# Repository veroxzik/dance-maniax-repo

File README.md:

# Dance Maniax Repo

A collection of Dance Maniax related items, both from the arcade cabinet and DIY.

**Disclaimer:** I am measuring all these parts by hand, so they may not be 100% accurate (although I try hard). There's no warranty given to anything contained in this repo, so use at your own risk!

## CAD

So far, I only have CAD of the lower sensor assembly. It's uploaded in \*.f3z and \*.stp file.

For planning purposes, I've also included the following image for approximate sensor locations, relative to each other.

## Boards

Likewise, only the boards in the sensor assembly have been reverse engineered.

GX874-PWB(J) is the board which diverts power to the LEDs.

GX874-PWB(I) provides a mounting point for the LEDs and their connector.

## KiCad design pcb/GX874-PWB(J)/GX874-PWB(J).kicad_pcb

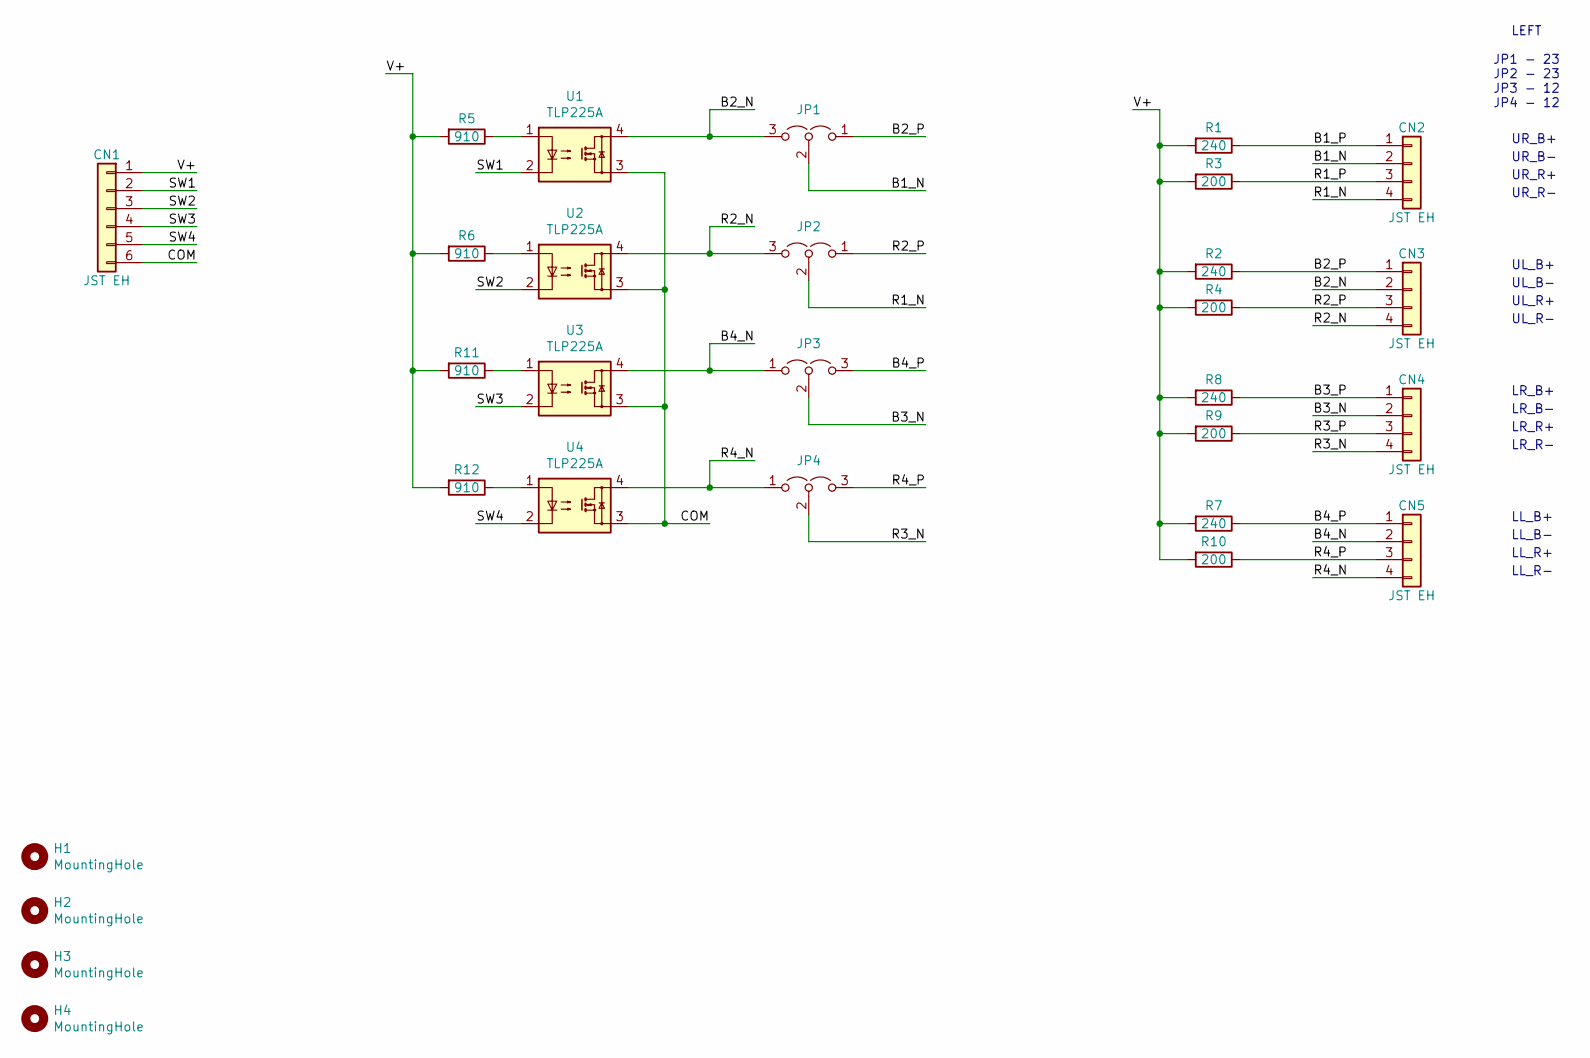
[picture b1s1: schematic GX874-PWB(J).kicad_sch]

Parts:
CN1: JST EH; JST_EH_B6B-EH-A_1x06_P2.50mm_Vertical
CN2, CN3, CN4, CN5: JST EH; JST_EH_B4B-EH-A_1x04_P2.50mm_Vertical
H1, H2, H3, H4: MountingHole; MountingHole_3.2mm_M3_DIN965
JP1, JP2, JP3, JP4: Jumper_3_Open; PinHeader_1x03_P2.54mm_Vertical
R1, R2, R7, R8: 240; R_Axial_DIN0207_L6.3mm_D2.5mm_P10.16mm_Horizontal
R3, R4, R9, R10: 200; R_Axial_DIN0207_L6.3mm_D2.5mm_P10.16mm_Horizontal
R5, R6, R11, R12: 910; R_Axial_DIN0207_L6.3mm_D2.5mm_P10.16mm_Horizontal
U1, U2, U3, U4: TLP225A; DIP-4_W7.62mm

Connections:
/B1_N: CN2.2, JP1.2 (C)
/B1_P: CN2.1, R1.1
/B2_N: CN3.2, JP1.3 (B), U1.4
/B2_P: CN3.1, JP1.1 (A), R2.1
/B3_N: CN4.2, JP3.2 (C)
/B3_P: CN4.1, R8.1
/B4_N: CN5.2, JP3.1 (A), U3.4
/B4_P: CN5.1, JP3.3 (B), R7.1
/COM: CN1.6, U1.3, U2.3, U3.3, U4.3
/R1_N: CN2.4, JP2.2 (C)
/R1_P: CN2.3, R3.1
/R2_N: CN3.4, JP2.3 (B), U2.4
/R2_P: CN3.3, JP2.1 (A), R4.1
/R3_N: CN4.4, JP4.2 (C)
/R3_P: CN4.3, R9.1
/R4_N: CN5.4, JP4.1 (A), U4.4
/R4_P: CN5.3, JP4.3 (B), R10.1
/SW1: CN1.2, U1.2
/SW2: CN1.3, U2.2
/SW3: CN1.4, U3.2
/SW4: CN1.5, U4.2
/V+: CN1.1, R1.2, R2.2, R3.2, R4.2, R5.2, R6.2, R7.2, R8.2, R9.2, R10.2, R11.2, R12.2
unnamed: R5.1, U1.1
unnamed: R6.1, U2.1
unnamed: R11.1, U3.1
unnamed: R12.1, U4.1

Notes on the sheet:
LR_B+
JP1 - 23 JP2 - 23 JP3 - 12 JP4 - 12
UR_R-
LR_B-
UR_R+
LEFT
UL_R+
LL_R+
UR_B-
UR_B+
LL_R-
UL_R-
LL_B+
LL_B-
LR_R+
UL_B-
LR_R-
UL_B+

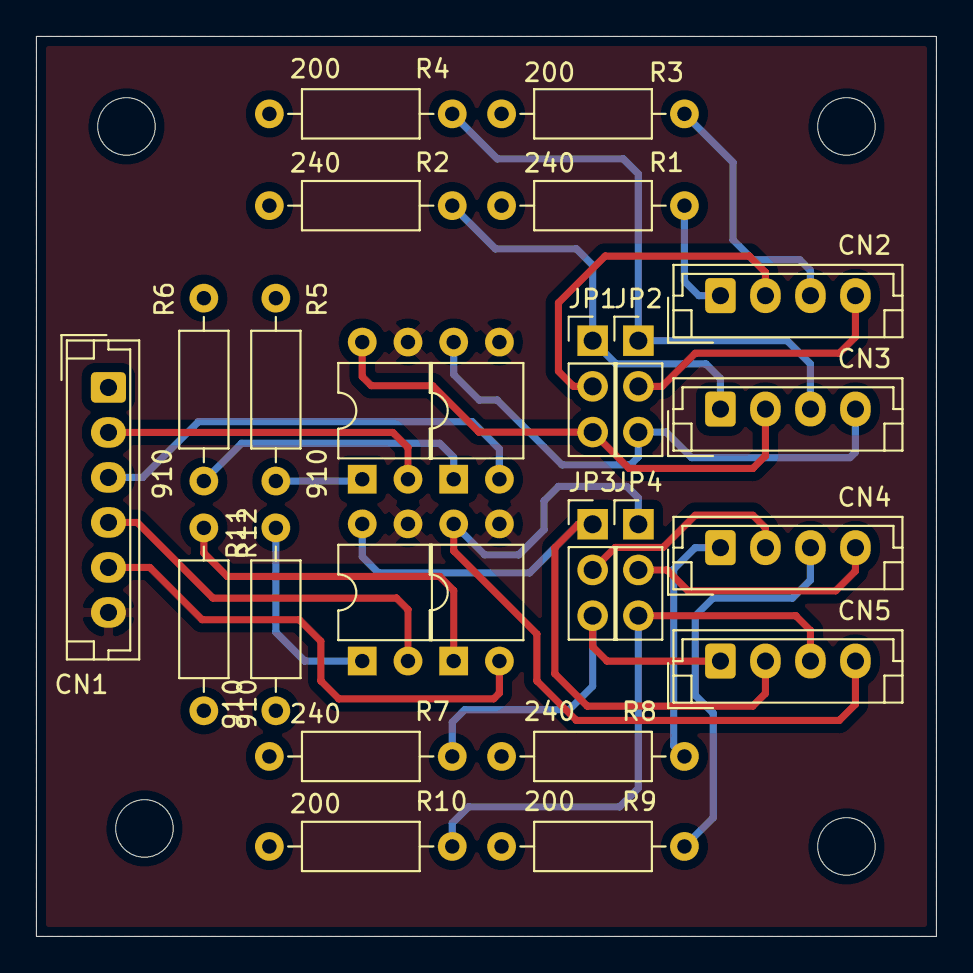
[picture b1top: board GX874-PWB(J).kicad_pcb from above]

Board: 2 copper layers, 50.0 x 50.0 mm, 29 parts (0 on the bottom side), 26 nets.

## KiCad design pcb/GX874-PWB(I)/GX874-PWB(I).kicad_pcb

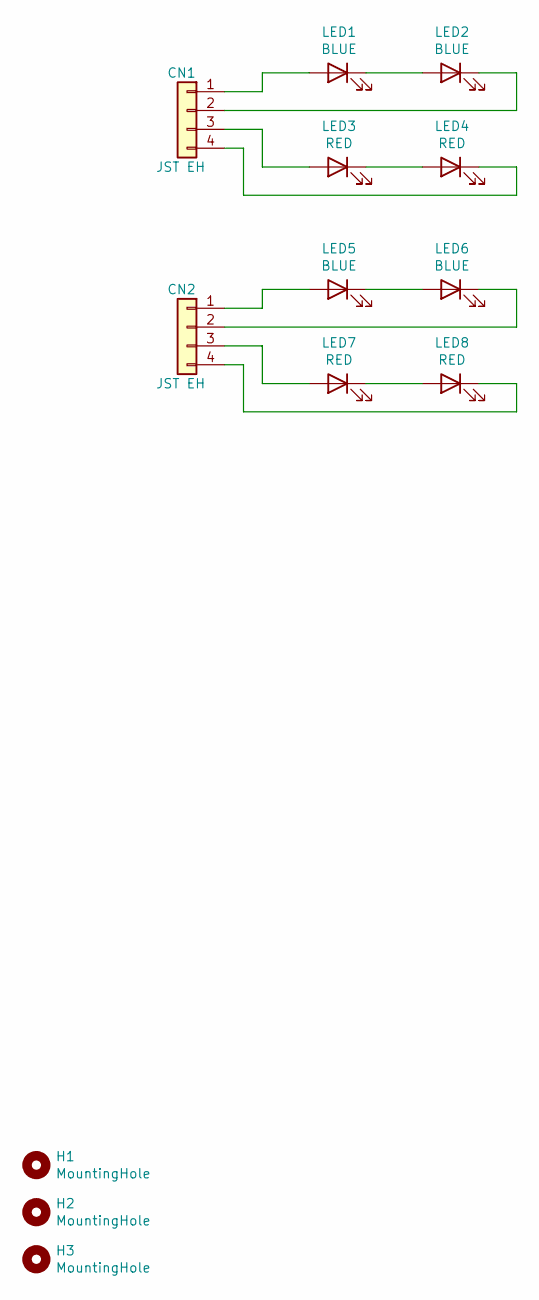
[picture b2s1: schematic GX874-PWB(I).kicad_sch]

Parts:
CN1, CN2: JST EH; JST_EH_B4B-EH-A_1x04_P2.50mm_Vertical
H1, H2, H3: MountingHole; MountingHole_3.2mm_M3_DIN965
LED1, LED2, LED5, LED6: BLUE; LED_D5.0mm
LED3, LED4, LED7, LED8: RED; LED_D5.0mm

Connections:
unnamed: CN1.1, LED1.2 (A)
unnamed: CN1.2, LED2.1 (K)
unnamed: CN1.3, LED3.2 (A)
unnamed: CN1.4, LED4.1 (K)
unnamed: CN2.1, LED5.2 (A)
unnamed: CN2.2, LED6.1 (K)
unnamed: CN2.3, LED7.2 (A)
unnamed: CN2.4, LED8.1 (K)
unnamed: LED1.1 (K), LED2.2 (A)
unnamed: LED3.1 (K), LED4.2 (A)
unnamed: LED5.1 (K), LED6.2 (A)
unnamed: LED7.1 (K), LED8.2 (A)

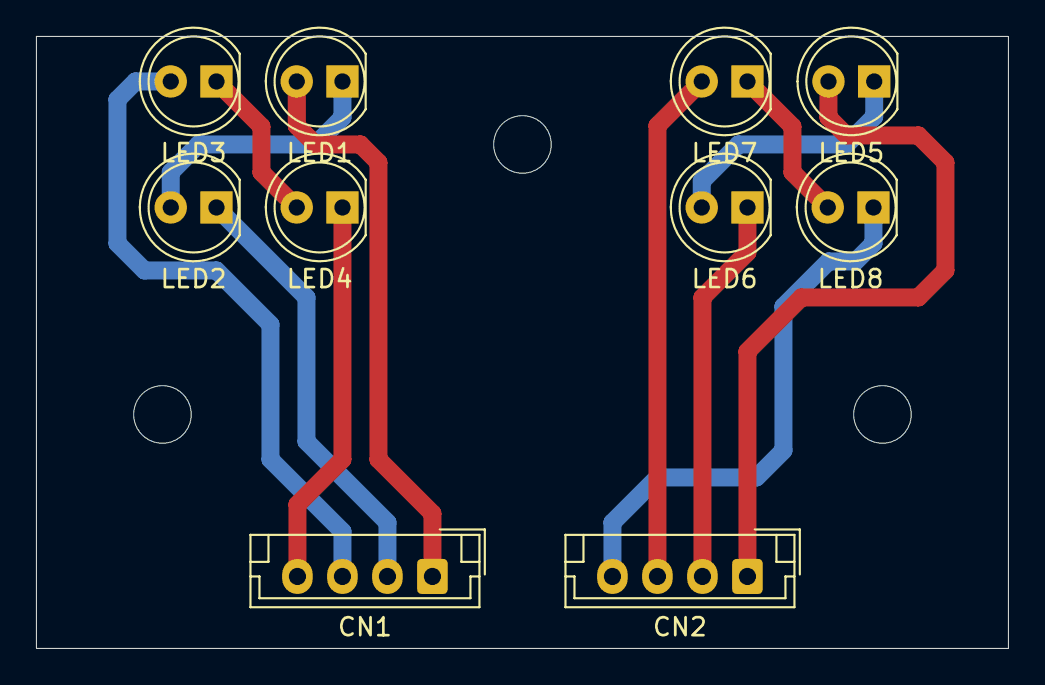
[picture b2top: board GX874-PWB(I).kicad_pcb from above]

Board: 2 copper layers, 54.0 x 34.0 mm, 13 parts (0 on the bottom side), 12 nets.
